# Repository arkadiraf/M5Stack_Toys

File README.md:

# M5Stack_Toys
 M5Stack based toys

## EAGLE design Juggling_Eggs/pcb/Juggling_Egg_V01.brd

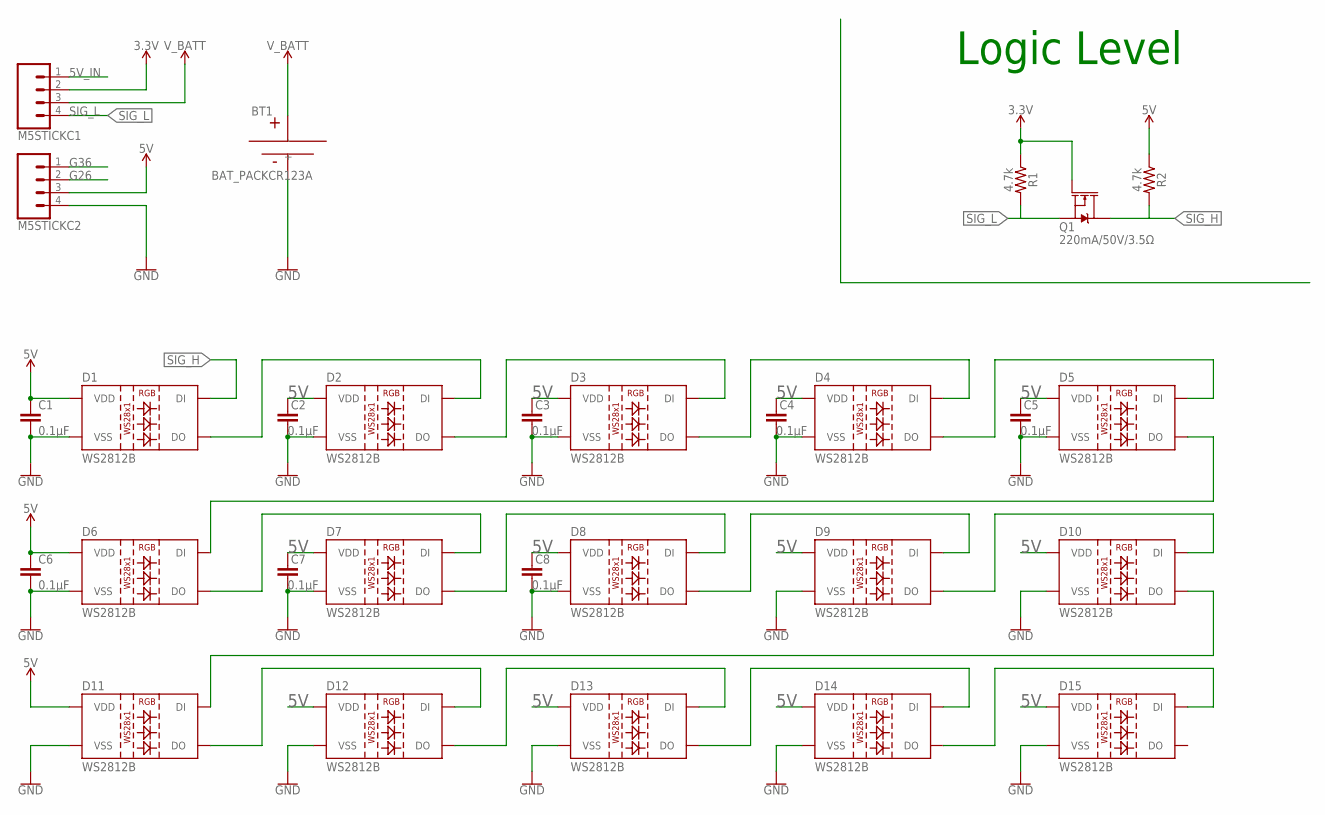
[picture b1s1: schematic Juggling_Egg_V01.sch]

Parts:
BT1: BAT_PACKCR123A; BH123A
C1, C2, C3, C4, C5, C6, C7, C8: 0.1µF; 0805
D1, D2, D3, D4, D5, D6, D7, D8, D9, D10, D11, D12, D13, D14, D15: WS2812B
M5STICKC1, M5STICKC2: CONN_04SMD; 1X04_SMD_RA_MALE
Q1: 220mA/50V/3.5Ω; SOT23-3
R1, R2: 4.7k; 0805

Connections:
3.3V: M5STICKC1.2, Q1.1 (G), R1.1
5V: C1.1, C2.2, C3.2, C4.2, C5.2, C6.1, C7.2, C8.2, D1.1 (VDD), D2.1 (VDD), D3.1 (VDD), D4.1 (VDD), D5.1 (VDD), D6.1 (VDD), D7.1 (VDD), D8.1 (VDD), D9.1 (VDD), D10.1 (VDD), D11.1 (VDD), D12.1 (VDD), D13.1 (VDD), D14.1 (VDD), D15.1 (VDD), M5STICKC2.3, R2.1
5V_IN: M5STICKC1.1
G26: M5STICKC2.2
G36: M5STICKC2.1
GND: BT1.-, C1.2, C2.1, C3.1, C4.1, C5.1, C6.2, C7.1, C8.1, D1.3 (VSS), D2.3 (VSS), D3.3 (VSS), D4.3 (VSS), D5.3 (VSS), D6.3 (VSS), D7.3 (VSS), D8.3 (VSS), D9.3 (VSS), D10.3 (VSS), D11.3 (VSS), D12.3 (VSS), D13.3 (VSS), D14.3 (VSS), D15.3 (VSS), M5STICKC2.4
unnamed: D2.2 (DO), D3.4 (DI)
unnamed: D3.2 (DO), D4.4 (DI)
unnamed: D4.2 (DO), D5.4 (DI)
unnamed: D6.2 (DO), D7.4 (DI)
unnamed: D1.2 (DO), D2.4 (DI)
unnamed: D7.2 (DO), D8.4 (DI)
unnamed: D8.2 (DO), D9.4 (DI)
unnamed: D9.2 (DO), D10.4 (DI)
unnamed: D11.2 (DO), D12.4 (DI)
unnamed: D12.2 (DO), D13.4 (DI)
unnamed: D13.2 (DO), D14.4 (DI)
unnamed: D14.2 (DO), D15.4 (DI)
unnamed: D5.2 (DO), D6.4 (DI)
unnamed: D10.2 (DO), D11.4 (DI)
SIG_H: D1.4 (DI), Q1.3 (D), R2.2
SIG_L: M5STICKC1.4, Q1.2 (S), R1.2
V_BATT: BT1.+, M5STICKC1.3

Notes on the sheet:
Logic Level

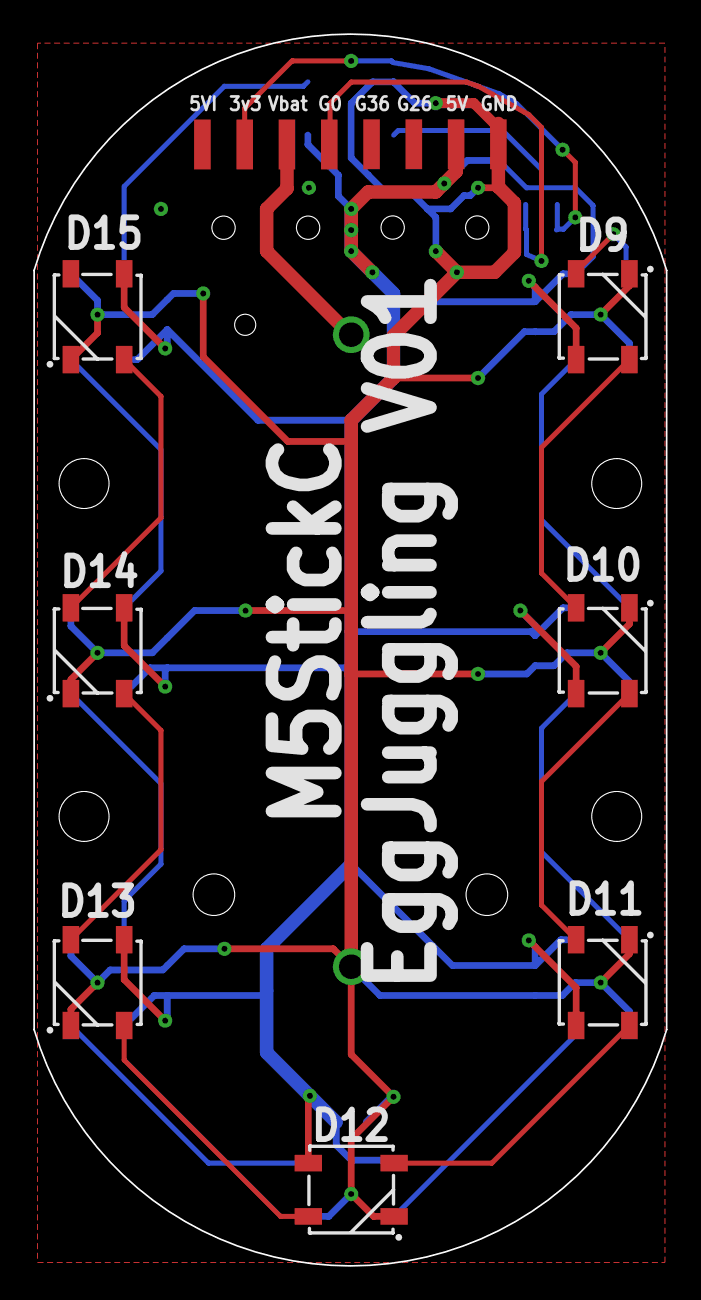
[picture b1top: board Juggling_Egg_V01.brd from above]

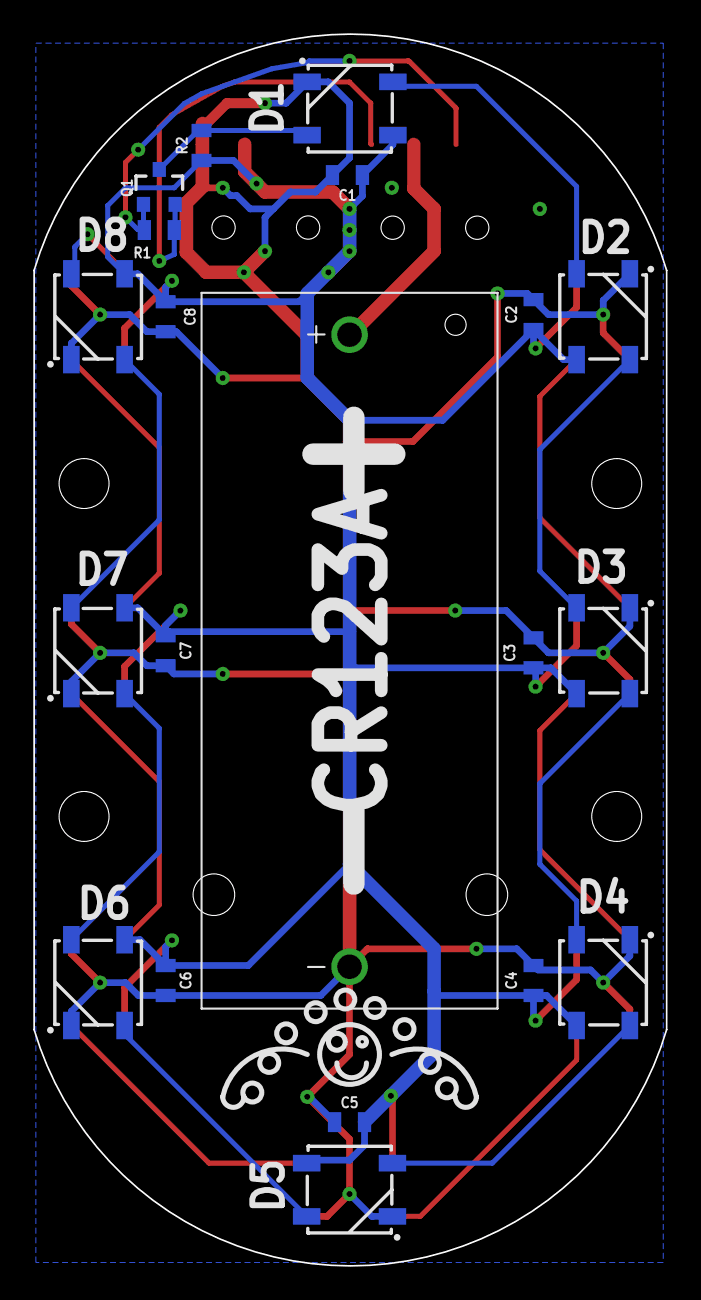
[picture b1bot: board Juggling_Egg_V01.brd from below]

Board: 2 copper layers, 38.0 x 74.0 mm, 29 parts (20 on the bottom side), 20 nets.

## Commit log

2020-03-01 Init Commit
2021-01-20 roverc
2021-02-08 roverc ref with minor changes
2021-03-18 juggling eggs
2021-07-26 minor changes
2023-04-07 esp32 mic
2023-04-12 stable version
2024-02-19 wifi example
2024-11-20 AccPlot

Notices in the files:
parts and their libraries:
SparkFun-Capacitors: Licensing: Creative Commons ShareAlike 4.0 International - https://creativecommons.org/licenses/by-sa/4.0
